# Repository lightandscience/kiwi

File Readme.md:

## WS2812b strip connector boards

Mostly passive boards, to solder to WS2812b LED strips, so strings of them can be connected.

Source for the kiwi svg (public domain): https://openclipart.org/detail/247170/kiwi-bird

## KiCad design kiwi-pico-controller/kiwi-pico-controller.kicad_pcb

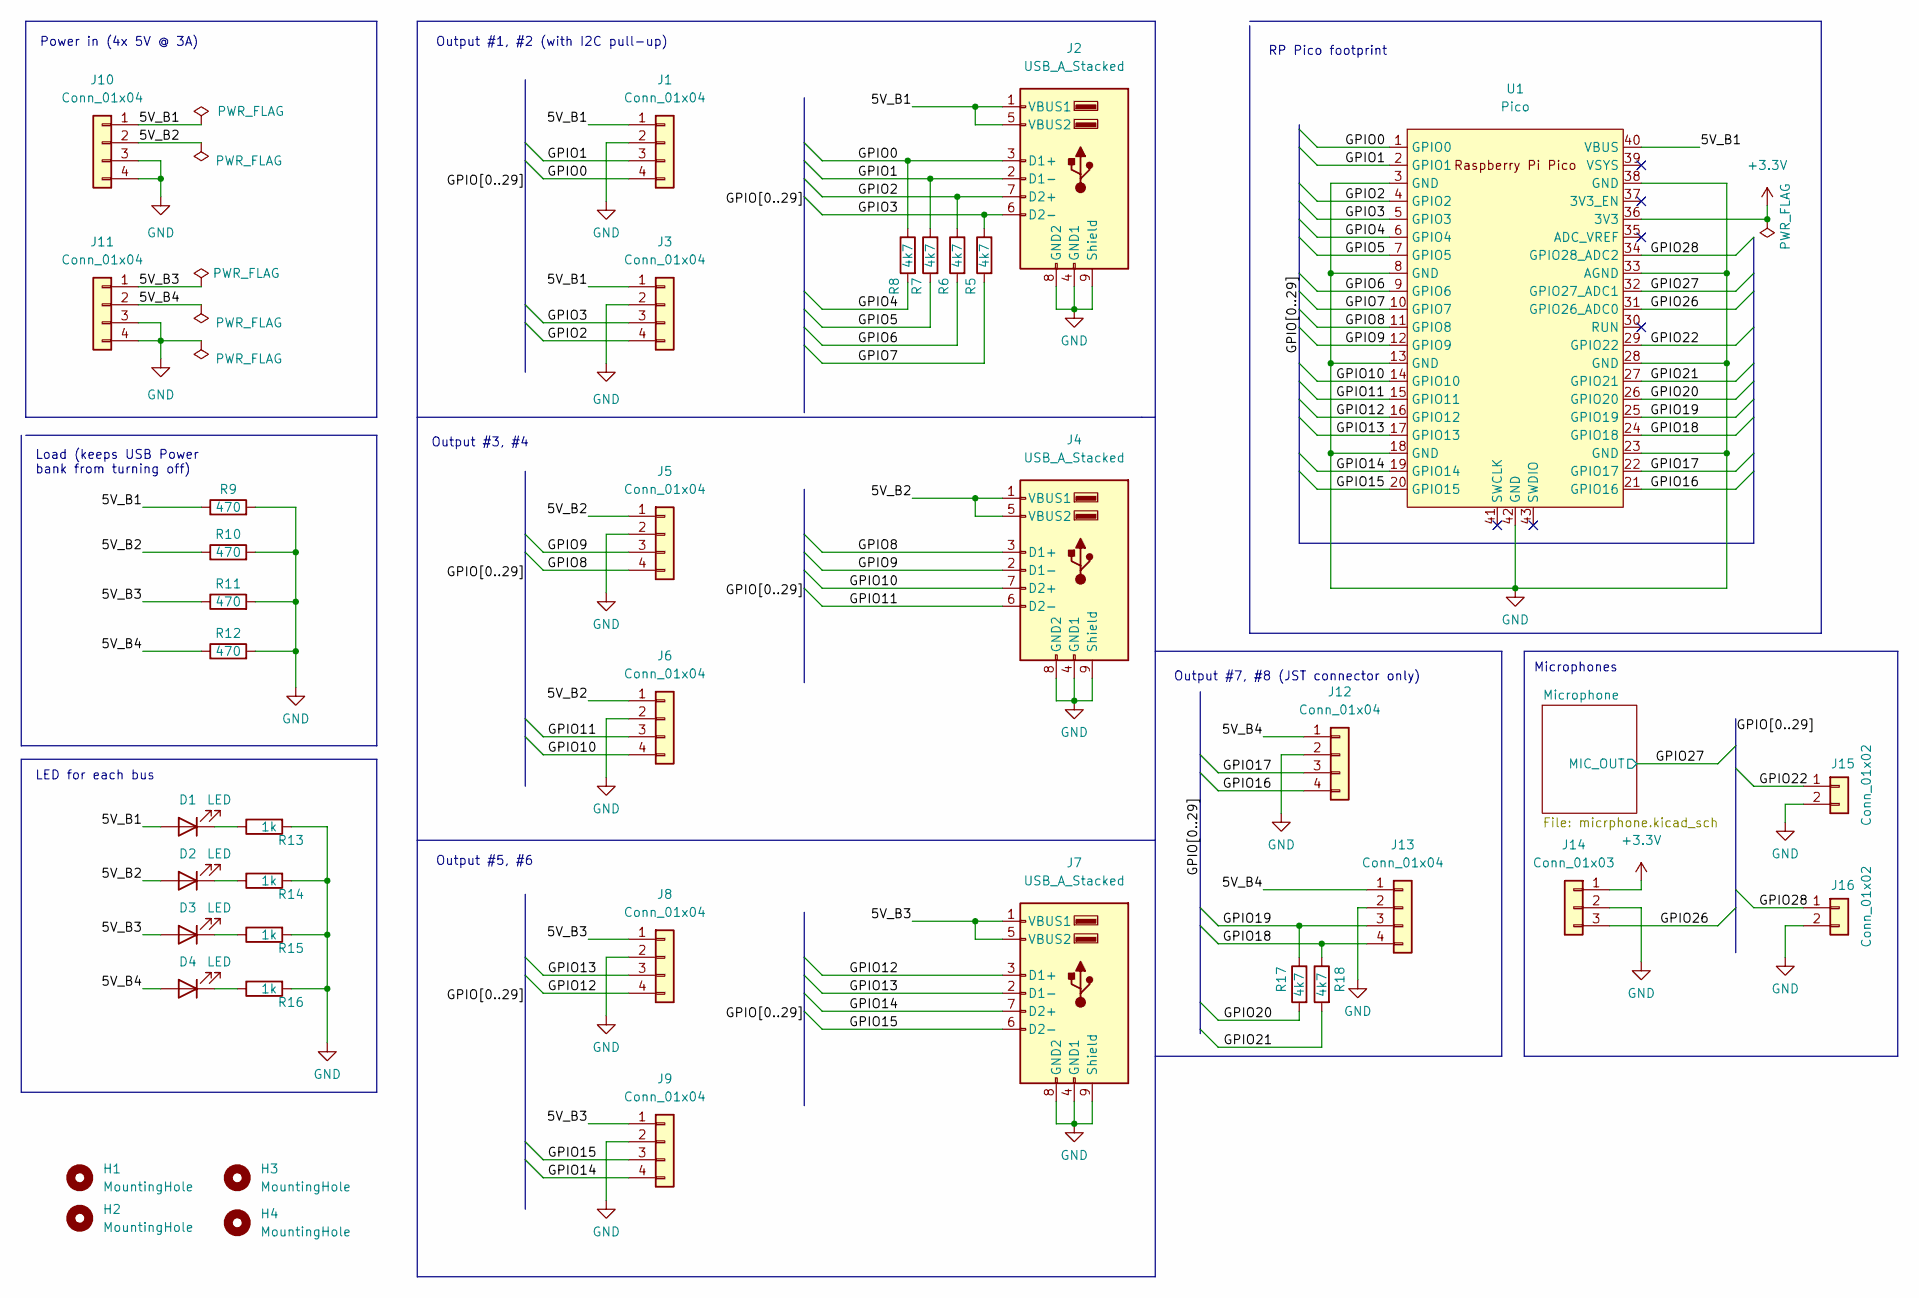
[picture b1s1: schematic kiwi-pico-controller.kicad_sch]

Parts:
D1, D2, D3, D4: LED; LED_0805_2012Metric_Pad1.15x1.40mm_HandSolder
H1, H2, H3, H4: MountingHole; MountingHole_2.5mm
J1, J3, J5, J6, J8, J9, J12, J13: Conn_01x04; JST_PH_B4B-PH-K_1x04_P2.00mm_Vertical
J2, J4, J7: USB_A_Stacked; USB_A_Wuerth_61400826021_Horizontal_Stacked
J10, J11: Conn_01x04; JST_XH_S4B-XH-A_1x04_P2.50mm_Horizontal
J14: Conn_01x03; JST_PH_B3B-PH-K_1x03_P2.00mm_Vertical
J15, J16: Conn_01x02; JST_PH_B2B-PH-K_1x02_P2.00mm_Vertical
R5, R6, R7, R8, R17, R18: 4k7; R_0805_2012Metric_Pad1.20x1.40mm_HandSolder
R9, R10, R11, R12: 470; R_Axial_DIN0207_L6.3mm_D2.5mm_P10.16mm_Horizontal
R13, R14, R15, R16: 1k; R_0805_2012Metric_Pad1.20x1.40mm_HandSolder
U1: Pico; RPi_Pico_SMD_TH

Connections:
+3.3V: J14.1, U1.36 (3V3); also elsewhere on the board
/5V_B1: D1.2 (A), J1.1, J2.1 (VBUS1), J2.5 (VBUS2), J3.1, J10.1, R9.1, U1.40 (VBUS)
/5V_B2: D2.2 (A), J4.1 (VBUS1), J4.5 (VBUS2), J5.1, J6.1, J10.2, R10.1
/5V_B3: D3.2 (A), J7.1 (VBUS1), J7.5 (VBUS2), J8.1, J9.1, J11.1, R11.1
/5V_B4: D4.2 (A), J11.2, J12.1, J13.1, R12.1
/GPIO0: J1.4, J2.3 (D1+), R8.1, U1.1 (GPIO0)
/GPIO1: J1.3, J2.2 (D1-), R7.1, U1.2 (GPIO1)
/GPIO2: J2.7 (D2+), J3.4, R6.1, U1.4 (GPIO2)
/GPIO3: J2.6 (D2-), J3.3, R5.1, U1.5 (GPIO3)
/GPIO4: R8.2, U1.6 (GPIO4)
/GPIO5: R7.2, U1.7 (GPIO5)
/GPIO6: R6.2, U1.9 (GPIO6)
/GPIO7: R5.2, U1.10 (GPIO7)
/GPIO8: J4.3 (D1+), J5.4, U1.11 (GPIO8)
/GPIO9: J4.2 (D1-), J5.3, U1.12 (GPIO9)
/GPIO10: J4.7 (D2+), J6.4, U1.14 (GPIO10)
/GPIO11: J4.6 (D2-), J6.3, U1.15 (GPIO11)
/GPIO12: J7.3 (D1+), J8.4, U1.16 (GPIO12)
/GPIO13: J7.2 (D1-), J8.3, U1.17 (GPIO13)
/GPIO14: J7.7 (D2+), J9.4, U1.19 (GPIO14)
/GPIO15: J7.6 (D2-), J9.3, U1.20 (GPIO15)
/GPIO16: J12.4, U1.21 (GPIO16)
/GPIO17: J12.3, U1.22 (GPIO17)
/GPIO18: J13.4, R18.1, U1.24 (GPIO18)
/GPIO19: J13.3, R17.1, U1.25 (GPIO19)
/GPIO20: R17.2, U1.26 (GPIO20)
/GPIO21: R18.2, U1.27 (GPIO21)
/GPIO22: J15.1, U1.29 (GPIO22)
/GPIO26: J14.3, U1.31 (GPIO26_ADC0)
/GPIO27: U1.32 (GPIO27_ADC1); also elsewhere on the board
/GPIO28: J16.1, U1.34 (GPIO28_ADC2)
GND: J1.2, J2.4 (GND1), J2.8 (GND2), J2.9 (Shield), J3.2, J4.4 (GND1), J4.8 (GND2), J4.9 (Shield), J5.2, J6.2, J7.4 (GND1), J7.8 (GND2), J7.9 (Shield), J8.2, J9.2, J10.3, J10.4, J11.3, J11.4, J12.2, J13.2, J14.2, J15.2, J16.2, R9.2, R10.2, R11.2, R12.2, R13.2, R14.2, R15.2, R16.2, U1.3 (GND), U1.8 (GND), U1.13 (GND), U1.18 (GND), U1.23 (GND), U1.28 (GND), U1.33 (AGND), U1.38 (GND), U1.42 (GND); also elsewhere on the board
unnamed: D1.1 (K), R13.1
unnamed: D2.1 (K), R14.1
unnamed: D3.1 (K), R15.1
unnamed: D4.1 (K), R16.1

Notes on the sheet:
Output #5, #6
Load (keeps USB Power bank from turning off)
RP Pico footprint
Microphones
LED for each bus
Output #3, #4
Output #1, #2 (with I2C pull-up)
Output #7, #8 (JST connector only)
Power in (4x 5V @ 3A)

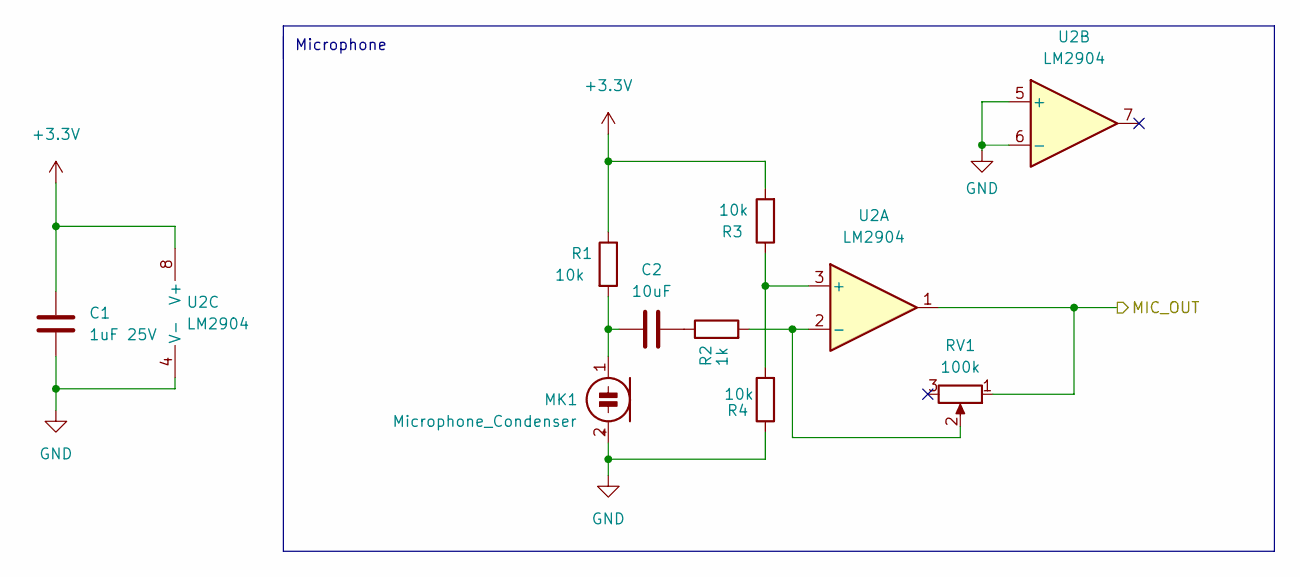
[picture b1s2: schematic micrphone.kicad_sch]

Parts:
C1: 1uF 25V; C_0805_2012Metric_Pad1.18x1.45mm_HandSolder
C2: 10uF; C_0805_2012Metric_Pad1.18x1.45mm_HandSolder
MK1: Microphone_Condenser; 6mm-Microphone
R1, R3, R4: 10k; R_0805_2012Metric_Pad1.20x1.40mm_HandSolder
R2: 1k; R_0805_2012Metric_Pad1.20x1.40mm_HandSolder
RV1: 100k; Potentiometer_Piher_PT-10-V05_Vertical
U2: LM2904; SO-8_3.9x4.9mm_P1.27mm

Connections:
+3.3V: C1.1, R1.1, R3.2, U2.8 (V+); also elsewhere on the board
/GPIO27: RV1.1, U2.1; also elsewhere on the board
GND: C1.2, MK1.2 (+), R4.1, U2.4 (V-), U2.5 (+), U2.6 (-); also elsewhere on the board
unnamed: C2.1, MK1.1 (-), R1.2
unnamed: C2.2, R2.1
unnamed: R2.2, RV1.2, U2.2 (-)
unnamed: R3.1, R4.2, U2.3 (+)

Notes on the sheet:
Microphone

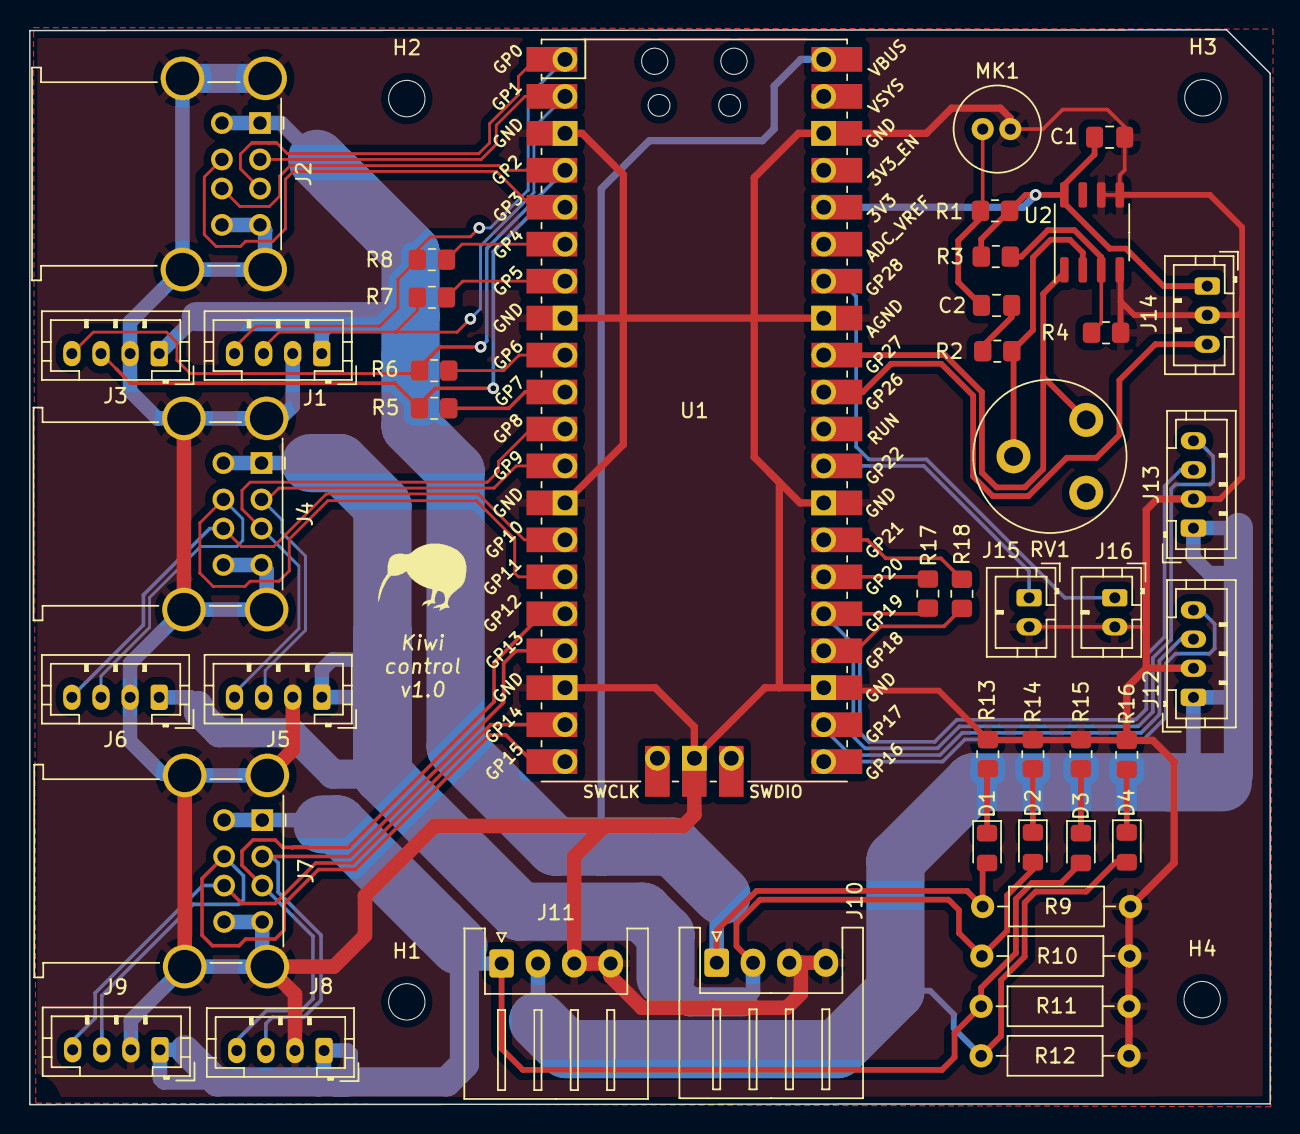
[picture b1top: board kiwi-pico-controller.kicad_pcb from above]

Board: 2 copper layers, 85.2 x 73.9 mm, 48 parts (0 on the bottom side), 40 nets.

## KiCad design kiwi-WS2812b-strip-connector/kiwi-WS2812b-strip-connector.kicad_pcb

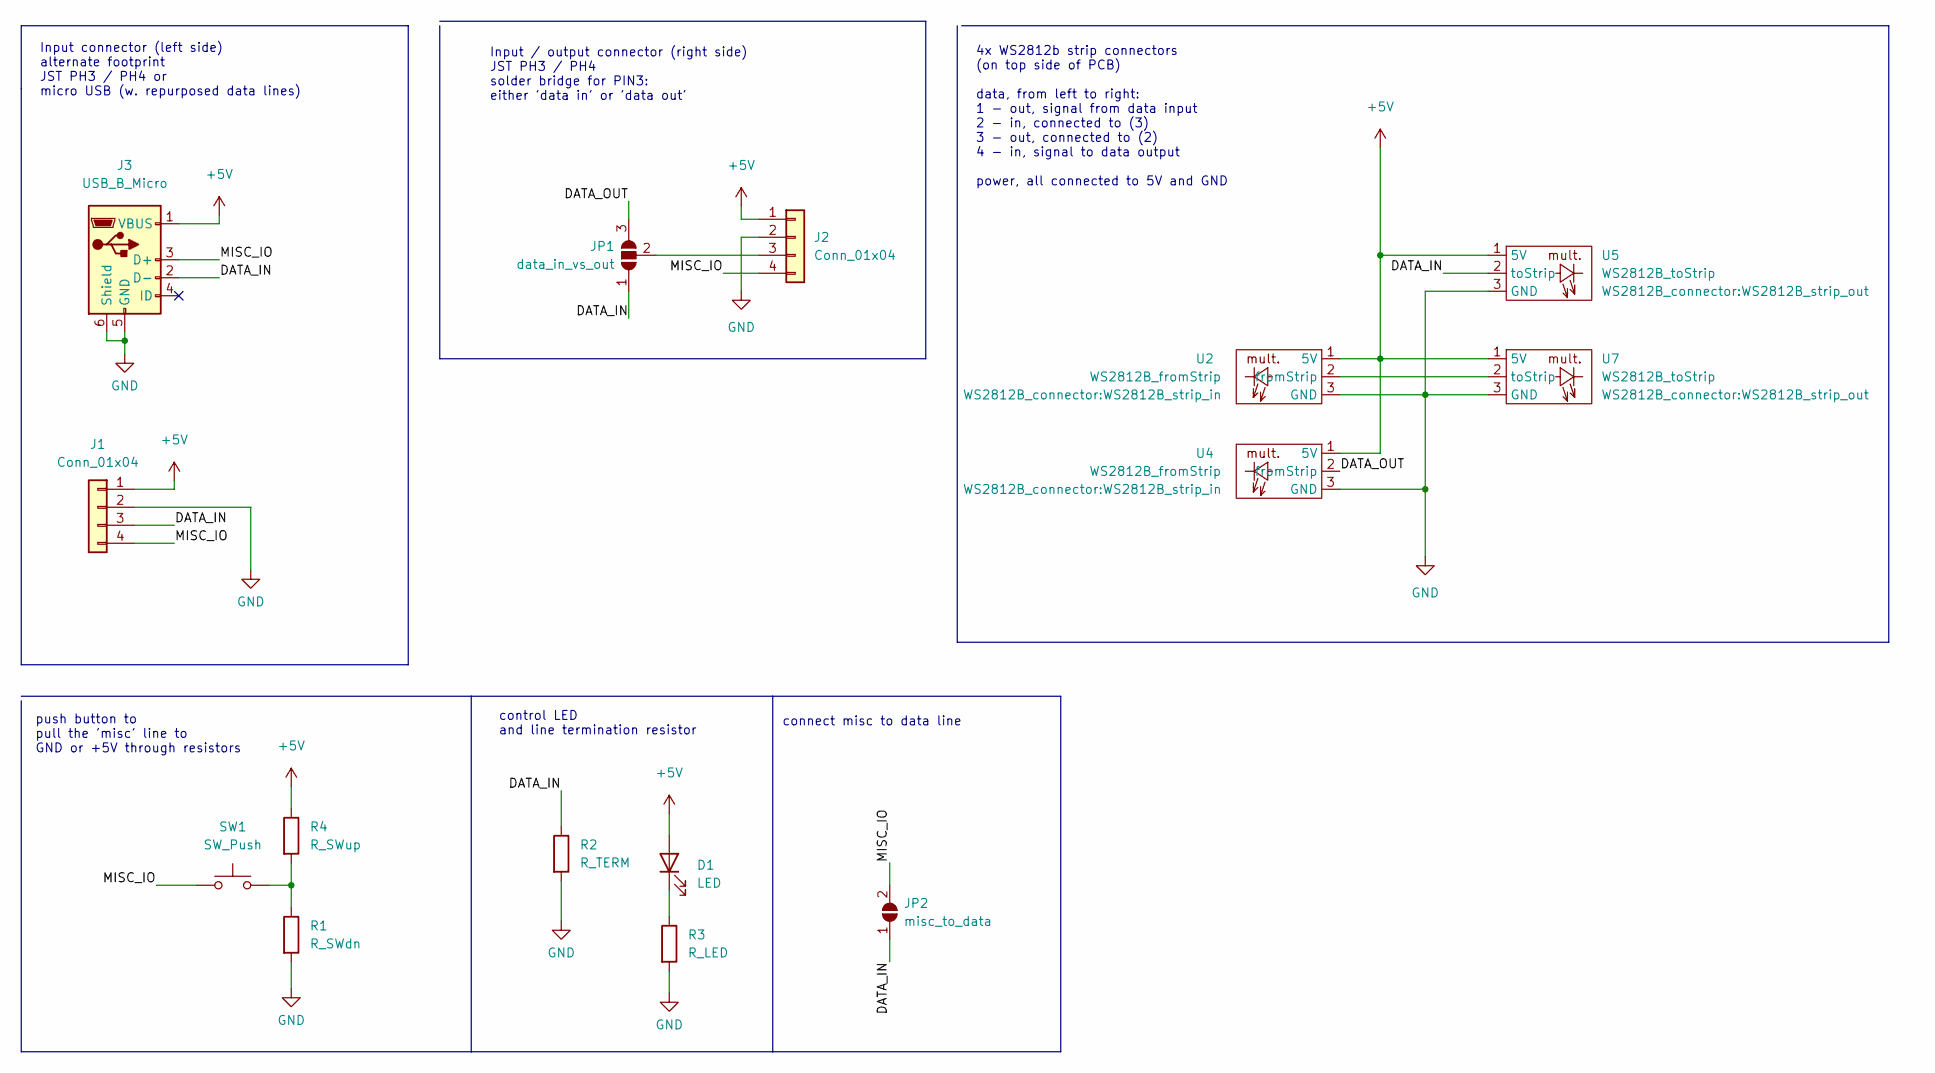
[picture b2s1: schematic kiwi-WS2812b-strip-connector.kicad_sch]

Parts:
D1: LED; LED_0805_2012Metric_Pad1.15x1.40mm_HandSolder
J1, J2: Conn_01x04; JST_PH_S4B-PH-K_1x04_P2.00mm_Horizontal
J3: USB_B_Micro; USB_Micro_MIUSB-F5M-BB-U
JP1: data_in_vs_out; SolderJumper-3_P1.3mm_Open_RoundedPad1.0x1.5mm
JP2: misc_to_data; SolderJumper-2_P1.3mm_Open_RoundedPad1.0x1.5mm
R1: R_SWdn; R_0805_2012Metric_Pad1.20x1.40mm_HandSolder
R2: R_TERM; R_0805_2012Metric_Pad1.20x1.40mm_HandSolder
R3: R_LED; R_0805_2012Metric_Pad1.20x1.40mm_HandSolder
R4: R_SWup; R_0805_2012Metric_Pad1.20x1.40mm_HandSolder
SW1: SW_Push; SW_PUSH_6mm
U2, U4: WS2812B_fromStrip; WS2812B_strip_in
U5, U7: WS2812B_toStrip; WS2812B_strip_out

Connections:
+5V: D1.2 (A), J1.1, J2.1, J3.1 (VBUS), R4.1, U2.1 (5V), U4.1 (5V), U5.1 (5V), U7.1 (5V)
/DATA_IN: J1.3, J3.2 (D-), JP1.1 (A), JP2.1 (A), R2.1, U5.2 (toStrip)
/DATA_OUT: JP1.3 (B), U4.2 (fromStrip)
/MISC_IO: J1.4, J2.4, J3.3 (D+), JP2.2 (B), SW1.1
GND: J1.2, J2.2, J3.5 (GND), J3.6 (Shield), R1.2, R2.2, R3.2, U2.3 (GND), U4.3 (GND), U5.3 (GND), U7.3 (GND)
unnamed: D1.1 (K), R3.1
unnamed: J2.3, JP1.2 (C)
unnamed: R1.1, R4.2, SW1.2
unnamed: U2.2 (fromStrip), U7.2 (toStrip)

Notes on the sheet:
Input / output connector (right side) JST PH3 / PH4 solder bridge for PIN3: either 'data in' or 'data out'
Input connector (left side) alternate footprint JST PH3 / PH4 or micro USB (w. repurposed data lines)
push button to pull the 'misc' line to GND or +5V through resistors
control LED and line termination resistor
4x WS2812b strip connectors (on top side of PCB) data, from left to right: 1 - out, signal from data input 2 - in, connected to (3) 3 - out, connected to (2) 4 - in, signal to data output power, all connected to 5V and GND
connect misc to data line

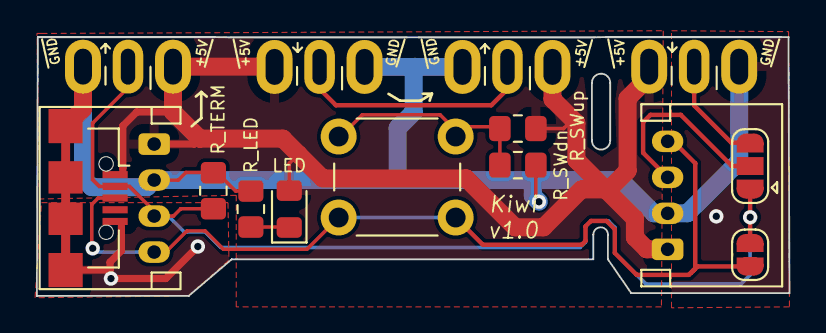
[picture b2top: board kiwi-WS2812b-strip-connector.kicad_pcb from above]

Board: 2 copper layers, 41.8 x 14.4 mm, 15 parts (0 on the bottom side), 9 nets.

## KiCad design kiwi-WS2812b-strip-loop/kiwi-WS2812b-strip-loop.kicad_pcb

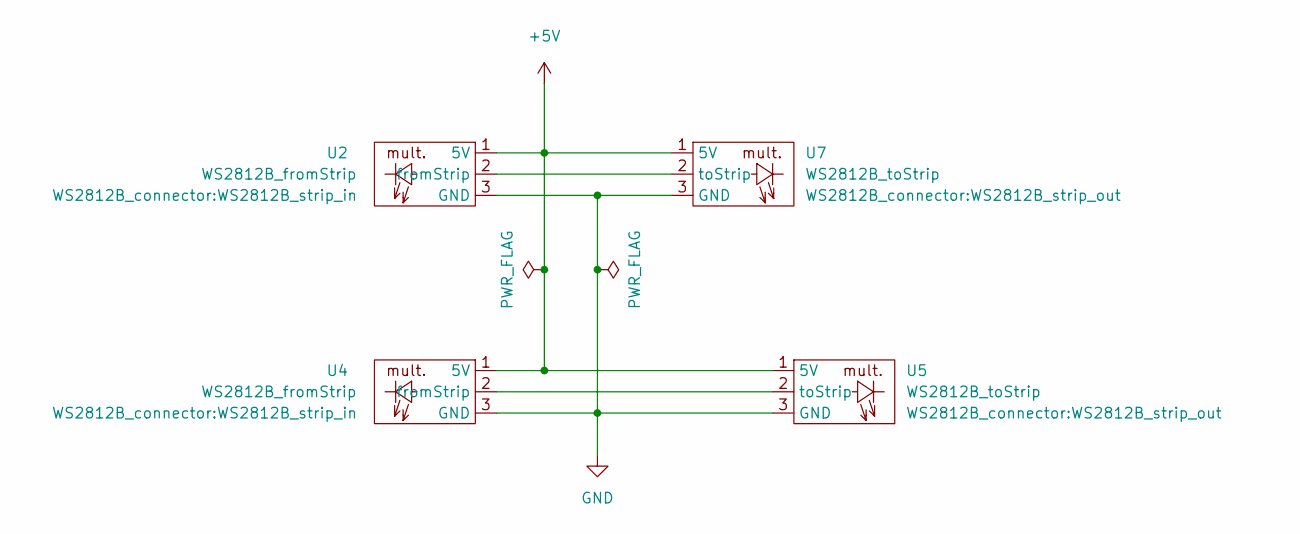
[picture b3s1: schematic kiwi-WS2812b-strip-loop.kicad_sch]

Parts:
U2, U4: WS2812B_fromStrip; WS2812B_strip_in
U5, U7: WS2812B_toStrip; WS2812B_strip_out

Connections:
+5V: U2.1 (5V), U4.1 (5V), U5.1 (5V), U7.1 (5V)
GND: U2.3 (GND), U4.3 (GND), U5.3 (GND), U7.3 (GND)
unnamed: U2.2 (fromStrip), U7.2 (toStrip)
unnamed: U4.2 (fromStrip), U5.2 (toStrip)

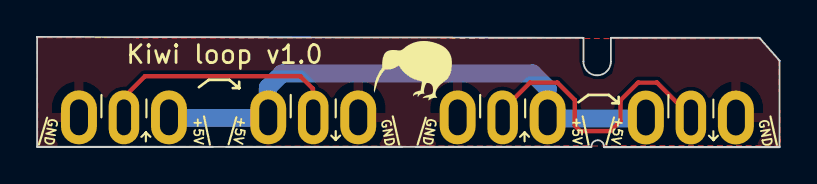
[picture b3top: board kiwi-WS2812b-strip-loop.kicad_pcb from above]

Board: 2 copper layers, 41.2 x 6.1 mm, 4 parts (0 on the bottom side), 4 nets.

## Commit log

2023-03-06 Initial version of the connector board
2023-03-06 Added the second 'loop' PCB
2023-03-08 Added USB connector as alternate footprint
2023-03-08 Commented schematics and updated PCB, both pass DRC
2023-03-09 Added first version of a controller board
    Board carrying a Raspberry Pico, set up to control (up to) 8 WS2812b
    LED strips.
